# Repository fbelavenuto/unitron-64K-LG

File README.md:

# unitron-64K-LG
Projeto para o micro Unitron 48K para substituição das RAMs por 4164 e Language Card

Documentação se encontra no artigo da OldPlayers:

https://oldplayers.com.br/wp/computadores/linha-apple/modificacao-4164-na-placa-do-unitron-48k/

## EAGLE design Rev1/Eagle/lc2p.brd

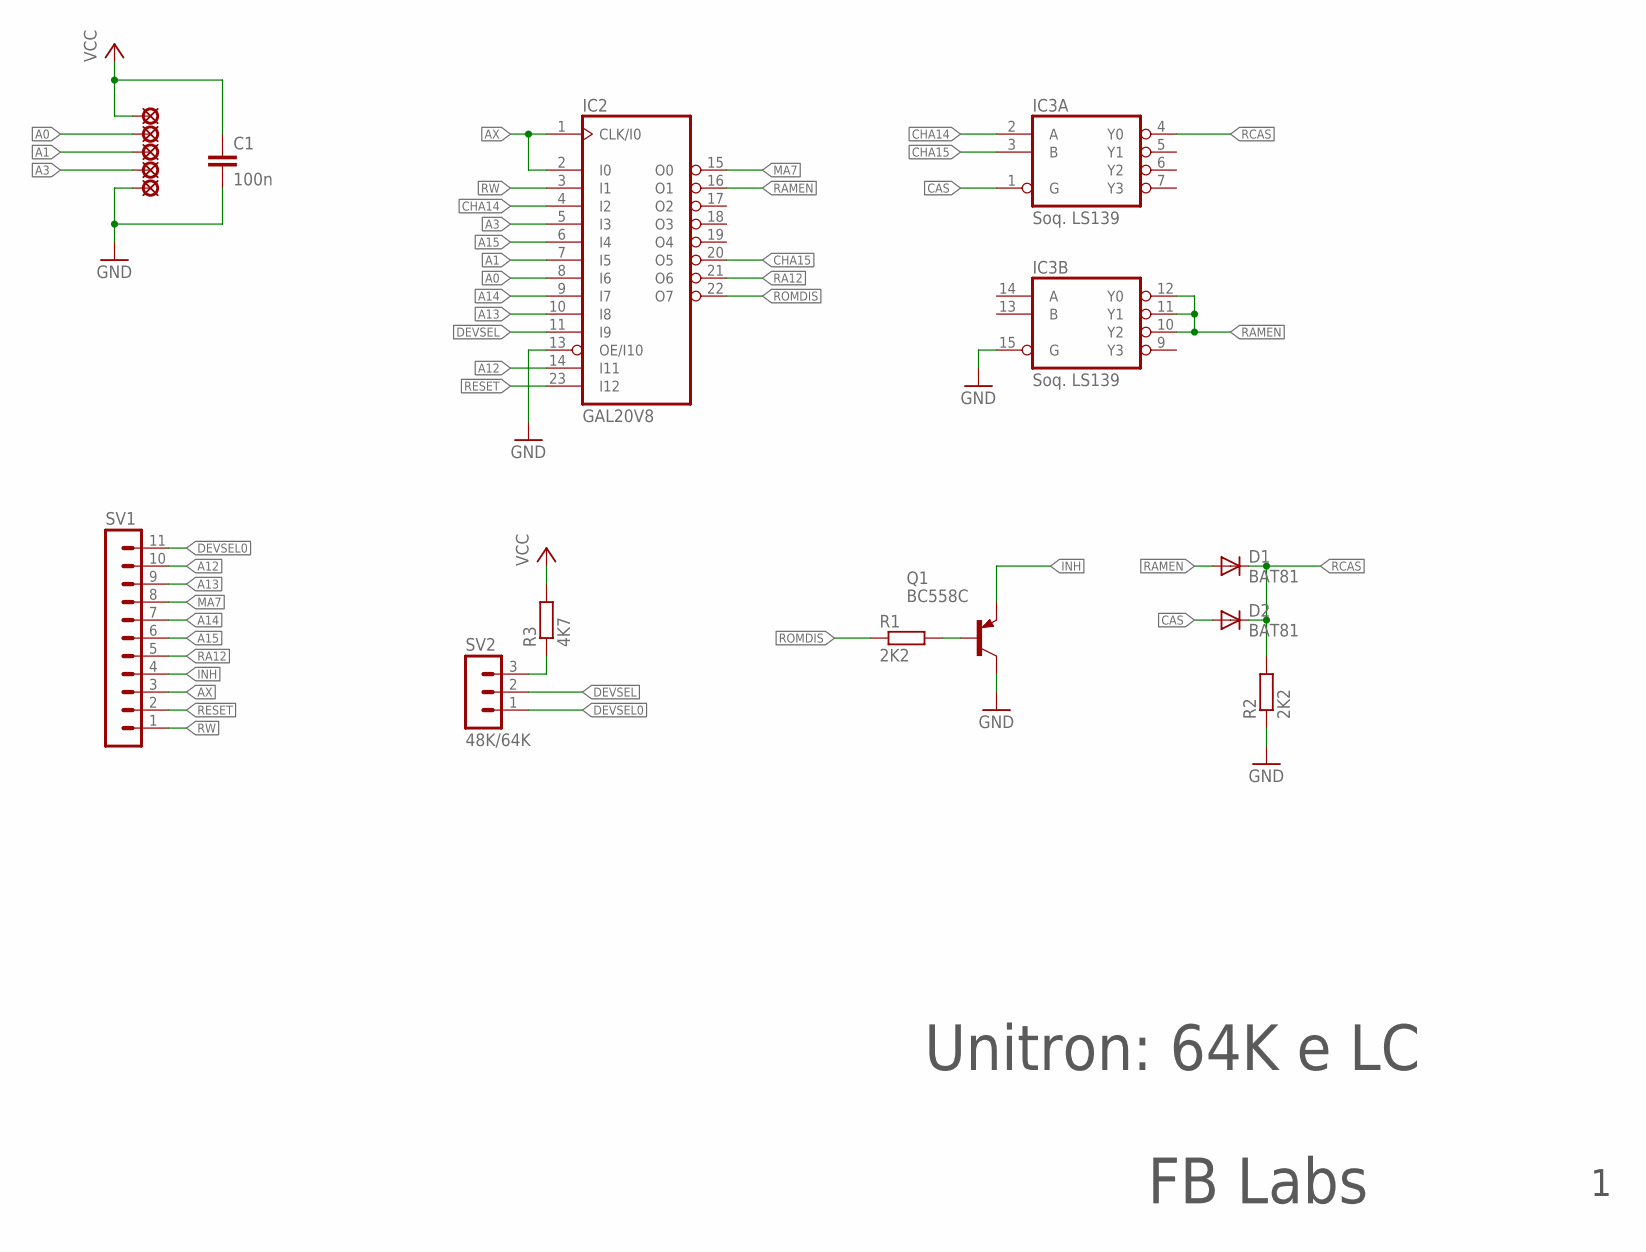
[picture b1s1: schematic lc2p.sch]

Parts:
C1: 100n; C050-024X044
D1, D2: BAT81; DO34-7
IC2: GAL20V8; DIL24-3
IC3: Soq. LS139; DIL16
LSP1, LSP2, LSP3, LSP4, LSP5: LSP10
Q1: BC558C; TO92-EBC
R1, R2: 2K2; 0207/7
R3: 4K7; 0207/7
SV1: MA11-1
SV2: 48K/64K; MA03-1-1

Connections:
!CAS: D2.A, IC3.1 (G)
!DEVSEL: IC2.11 (I9), SV2.2
!DEVSEL0: SV1.11, SV2.1
!INH: Q1.E, SV1.4
!RAMEN: D1.A, IC2.16 (O1), IC3.10 (Y2), IC3.11 (Y1), IC3.12 (Y0)
!RCAS: D1.C, D2.C, IC3.4 (Y0), R2.2
!RESET: IC2.23 (I12), SV1.2
A0: IC2.8 (I6), LSP1.MP
A1: IC2.7 (I5), LSP2.MP
A3: IC2.5 (I3), LSP3.MP
A12: IC2.14 (I11), SV1.10
A13: IC2.10 (I8), SV1.9
A14: IC2.9 (I7), SV1.7
A15: IC2.6 (I4), SV1.6
AX: IC2.1 (CLK/I0), IC2.2 (I0), SV1.3
CHA14: IC2.4 (I2), IC3.2 (A)
CHA15: IC2.20 (O5), IC3.3 (B)
GND: C1.2, IC2.12 (GND), IC2.13 (OE/I10), IC3.8 (GND), IC3.15 (G), LSP4.MP, Q1.C, R2.1
MA7: IC2.15 (O0), SV1.8
unnamed: R3.1, SV2.3
unnamed: Q1.B, R1.2
R!W: IC2.3 (I1), SV1.1
RA12: IC2.21 (O6), SV1.5
ROMDIS: IC2.22 (O7), R1.1
VCC: C1.1, IC2.24 (VCC), IC3.16 (VCC), LSP5.MP, R3.2

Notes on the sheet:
Unitron: 64K e LC
FB Labs

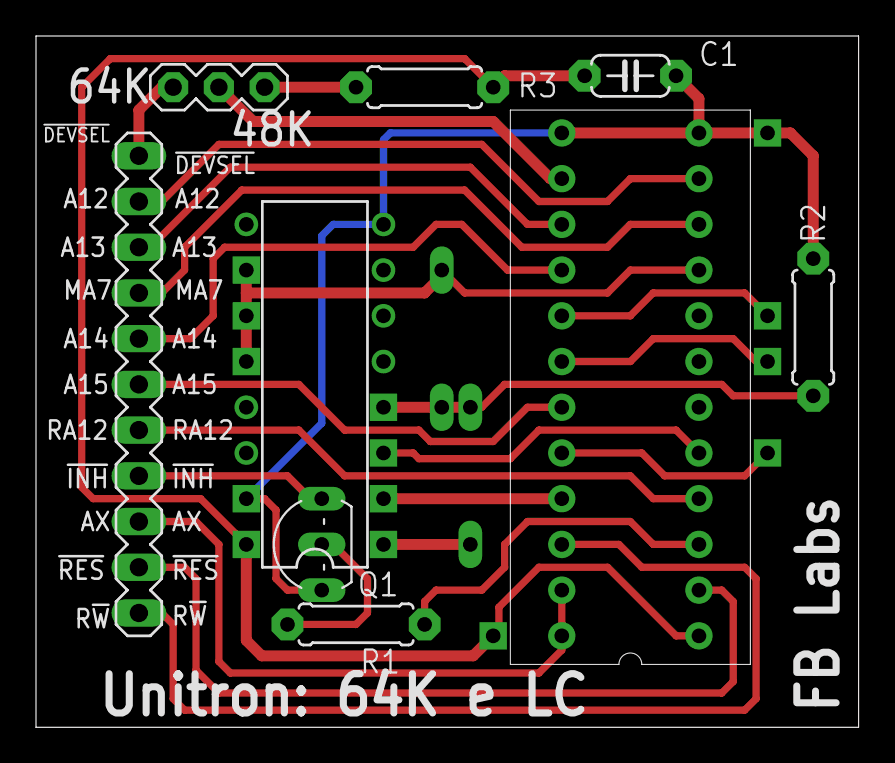
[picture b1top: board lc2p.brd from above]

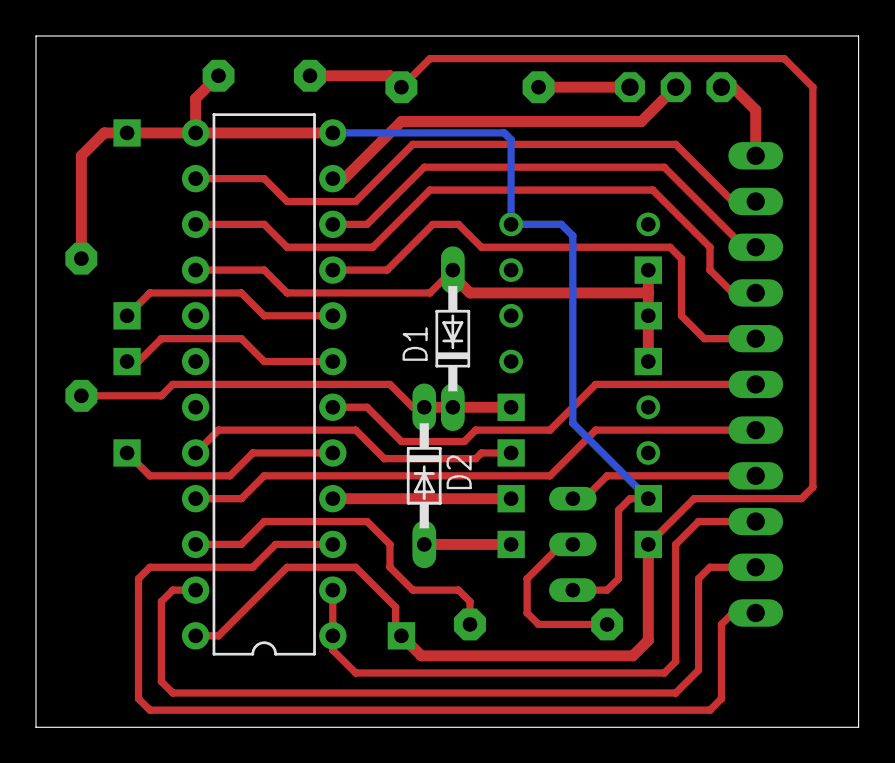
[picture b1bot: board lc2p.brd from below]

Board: 2 copper layers, 45.7 x 38.4 mm, 16 parts (3 on the bottom side), 25 nets.

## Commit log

2024-02-23 Envio iniciaç
